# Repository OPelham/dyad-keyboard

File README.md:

# Socius Keyboard

## Todo
Add reversable mcu mounting
Add reversable nice view mounting

Inspiration from the following projects:
https://github.com/duckyb/urchin/blob/master/README.md - layout

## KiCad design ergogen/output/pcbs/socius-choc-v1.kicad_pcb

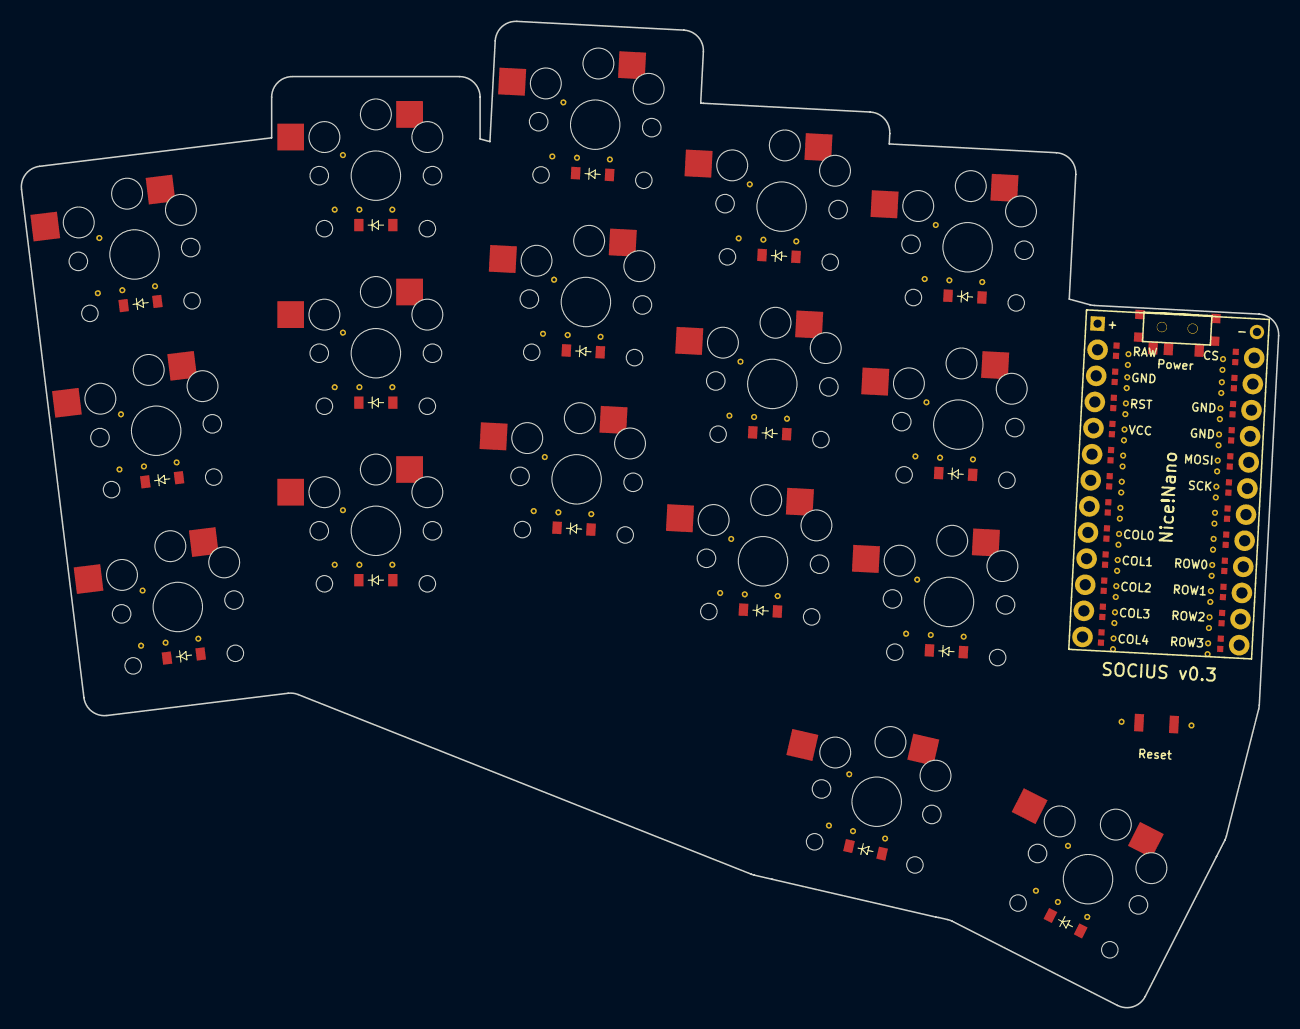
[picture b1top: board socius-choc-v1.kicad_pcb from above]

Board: 2 copper layers, 122.1 x 95.8 mm, 36 parts (0 on the bottom side), 28 nets, no tracks yet.

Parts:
D1, D2, D3, D4, D5, D6, D7, D8, D9, D10, D11, D12, D13, D14, D15, D16, D17: ComboDiode
MCU1: ProMicro
S1, S2, S3, S4, S5, S6, S7, S8, S9, S10, S11, S12, S13, S14, S15, S16, S17: PG1350
T1: SPDT_C128955

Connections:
COL0: MCU1.8, S1.1, S2.1, S3.1
COL1: MCU1.9, S4.1, S5.1, S6.1
COL2: MCU1.10, S7.1, S8.1, S9.1
COL3: MCU1.11, S10.1, S11.1, S12.1, S16.1
COL4: MCU1.12, S13.1, S14.1, S15.1, S17.1
GND: MCU1.2, MCU1.15, MCU1.16
RAW: MCU1.1, T1.1
ROW0: D3.1, D6.1, D9.1, D12.1, D15.1, MCU1.21
ROW1: D2.1, D5.1, D8.1, D11.1, D14.1, MCU1.22
ROW2: D1.1, D4.1, D7.1, D10.1, D13.1, MCU1.23
ROW3: D16.1, D17.1, MCU1.24
index_bottom: D10.2, S10.2
index_home: D11.2, S11.2
index_top: D12.2, S12.2
inner_bottom: D13.2, S13.2
inner_home: D14.2, S14.2
inner_sole: D16.2, S16.2
inner_top: D15.2, S15.2
middle_bottom: D7.2, S7.2
middle_home: D8.2, S8.2
middle_top: D9.2, S9.2
outer_sole: D17.2, S17.2
pinky_bottom: D1.2, S1.2
pinky_home: D2.2, S2.2
pinky_top: D3.2, S3.2
ring_bottom: D4.2, S4.2
ring_home: D5.2, S5.2
ring_top: D6.2, S6.2

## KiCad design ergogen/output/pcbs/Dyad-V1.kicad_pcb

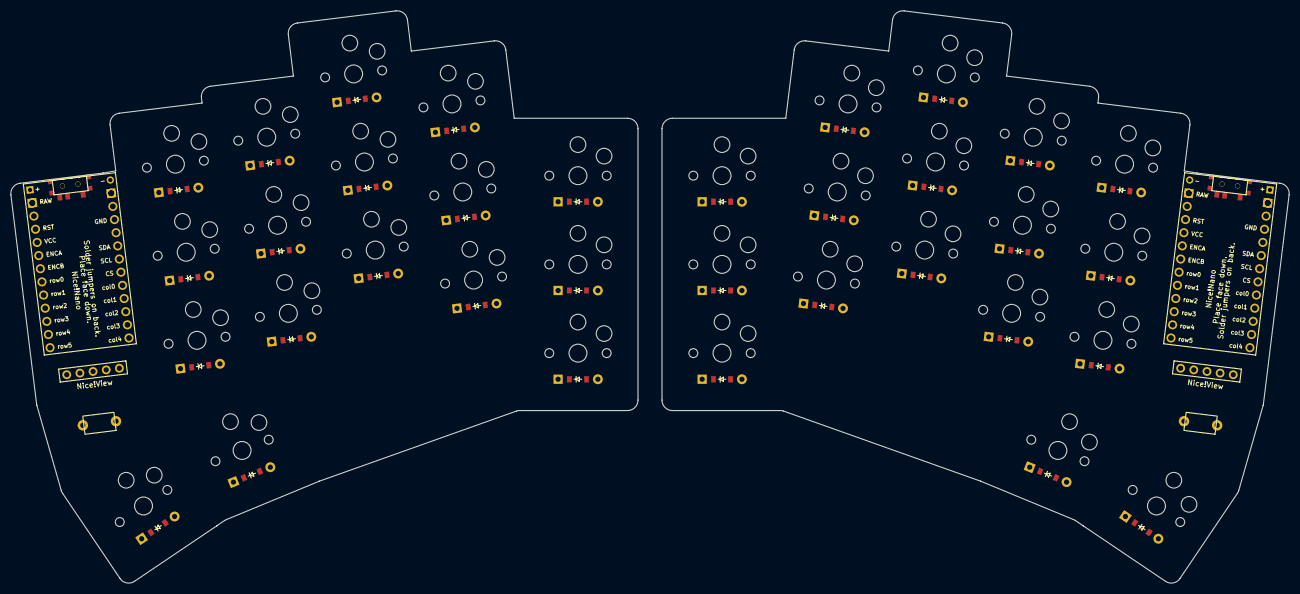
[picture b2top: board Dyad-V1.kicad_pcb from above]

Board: 2 copper layers, 244.9 x 109.6 mm, 74 parts (0 on the bottom side), 61 nets, no tracks yet.

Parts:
D1, D2, D3, D4, D5, D6, D7, D8, D9, D10, D11, D12, D13, D14, D15, D16, D17, D18, D19, D20, D21, D22, D23, D24, D25, D26, D27, D28, D29, D30, D31, D32, D33, D34: ComboDiode
MCU1, MCU2: ProMicro
Nice!View1, Nice!View2: niceview_headers
S1, S2, S3, S4, S5, S6, S7, S8, S9, S10, S11, S12, S13, S14, S15, S16, S17, S18, S19, S20, S21, S22, S23, S24, S25, S26, S27, S28, S29, S30, S31, S32, S33, S34: PG1350
T1, T2: SPDT_C128955

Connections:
GND: MCU1.2, MCU1.15, MCU1.16, MCU2.2, MCU2.15, MCU2.16
NN_CS_SDA: Nice!View1.1, Nice!View2.1
NN_GND_SCL: Nice!View1.1, Nice!View2.1
NN_SCL_GND: Nice!View1.3, Nice!View2.3
NN_SDA_CS: Nice!View1.4, Nice!View2.4
NN_VCC: Nice!View1.2, Nice!View2.2
P0: MCU1.14, MCU2.14
P1: MCU1.13, MCU2.13
P2: MCU1.17, MCU2.17
P3: MCU1.18, MCU2.18
P4: MCU1.19, MCU2.19
P5: MCU1.20, MCU2.20
P6: MCU1.21, MCU2.21
P7: MCU1.22, MCU2.22
P8: MCU1.23, MCU2.23
P9: MCU1.24, MCU2.24
P10: MCU1.12, MCU2.12
P14: MCU1.10, MCU2.10
P15: MCU1.9, MCU2.9
P16: MCU1.11, MCU2.11
P18: MCU1.8, MCU2.8
P19: MCU1.7, MCU2.7
P20: MCU1.6, MCU2.6
P21: MCU1.5, MCU2.5
RAW: MCU1.1, MCU2.1, T1.2, T2.2
RST: MCU1.3, MCU2.3
VCC: MCU1.4, MCU2.4
index_bottom: D10.2, S10.2
index_home: D11.2, S11.2
index_top: D12.2, S12.2
inner_bottom: D13.2, S13.2
inner_default: D16.2, S16.2
inner_home: D14.2, S14.2
inner_top: D15.2, S15.2
middle_bottom: D7.2, S7.2
middle_home: D8.2, S8.2
middle_top: D9.2, S9.2
mirror_index_bottom: D27.2, S27.2
mirror_index_home: D28.2, S28.2
mirror_index_top: D29.2, S29.2
mirror_inner_bottom: D30.2, S30.2
mirror_inner_default: D33.2, S33.2
mirror_inner_home: D31.2, S31.2
mirror_inner_top: D32.2, S32.2
mirror_middle_bottom: D24.2, S24.2
mirror_middle_home: D25.2, S25.2
mirror_middle_top: D26.2, S26.2
mirror_outer_default: D34.2, S34.2
mirror_pinkey_height_bottom: D18.2, S18.2
mirror_pinkey_height_home: D19.2, S19.2
mirror_pinkey_height_top: D20.2, S20.2
mirror_ring_bottom: D21.2, S21.2
mirror_ring_home: D22.2, S22.2
mirror_ring_top: D23.2, S23.2
outer_default: D17.2, S17.2
pinkey_height_bottom: D1.2, S1.2
pinkey_height_home: D2.2, S2.2
pinkey_height_top: D3.2, S3.2
ring_bottom: D4.2, S4.2
ring_home: D5.2, S5.2
ring_top: D6.2, S6.2
switch_from: T1.1, T2.1

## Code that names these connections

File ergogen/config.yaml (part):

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          reverse: true

      # Reversable MCU
      via-raw-pin-1:
        what: via
        where:
          ref: finger-zone_inner_home
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        params:
          net: RAW

      via-raw-pin-2:
        what: via
        where:
          ref: finger-zone_inner_home
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        params:
          net: P4

      via-col0-pin-1:
        what: via
        where:
          ref: finger-zone_inner_home
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        params:
          net: COL0

      via-col0-pin-2:
        what: via
        where:
          ref: finger-zone_inner_home
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        params:
          net: P5

      via-col1-pin-1:
        what: via
        where:
          ref: finger-zone_inner_home
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        params:
          net: COL1

      via-col1-pin-2:
        what: via
        where:
          ref: finger-zone_inner_home
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        params:
          net: COL1

      via-row0-pin-1:
        what: via
        where:
          ref: finger-zone_inner_home
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        params:
          net: ROW0

      via-row0-pin-2:
        what: via
        where:
          ref: finger-zone_inner_home
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        params:
          net: ROW0

      via-col2-pin-1:
        what: via
        where:
          ref: finger-zone_inner_home
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        params:
          net: COL2

      via-col2-pin-2:
        what: via
        where:
          ref: finger-zone_inner_home
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        params:
          net: COL2

      via-row1-pin-1:
        what: via
        where:
          ref: finger-zone_inner_home
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        params:
          net: ROW1

      via-row1-pin-2:
        what: via
        where:
          ref: finger-zone_inner_home
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        params:
          net: ROW1

      via-col3-pin-1:
        what: via
        where:
          ref: finger-zone_inner_home
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        params:
          net: COL3

      via-col3-pin-2:
        what: via
        where:
          ref: finger-zone_inner_home
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        params:
          net: COL3

      via-row2-pin-1:
        what: via
        where:
          ref: finger-zone_inner_home
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        params:
          net: ROW2

      via-row2-pin-2:
        what: via
        where:
          ref: finger-zone_inner_home
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        params:
          net: ROW2

      via-col4-pin-1:
        what: via
        where:
          ref: finger-zone_inner_home
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        params:
          net: COL4

      via-col4-pin-2:
        what: via
        where:
          ref: finger-zone_inner_home
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        params:
          net: COL4

      via-row3-pin-1:
        what: via
        where:
          ref: finger-zone_inner_home
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        params:
          net: ROW3

      via-row3-pin-2:
        what: via
        where:
          ref: finger-zone_inner_home
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
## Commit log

2024-02-25 Initial layout
2024-02-25 formatting
2024-02-25 label reformating
2024-02-25 adding text labels
2024-02-25 iterating routes
2024-02-25 completing routes
2024-02-26 continuing to refine
2024-02-26 adding via example
2024-03-02 Iterating design
2024-03-02 reversable design
2024-03-02 Rename and adding reverse side labels
2024-03-02 Rename
2024-03-03 iterating
2024-03-06 adding choc v2 compatibility
2024-03-06 adding reversable mcu
2024-03-06 routing reversable mcu
2024-03-14 adjusting dimensions after prototype 1
2024-10-24 altering key placement
